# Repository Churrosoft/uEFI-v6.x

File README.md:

# uEFI-v6.x
Speeduino compatible board, features:

* on board CAN
* SD card reader
* x4 ignition pre-drivers
* x4 injection channels
* 2&amp;4 wire IAC
* Accelerometer (ADXL343) / Barometer (BMP280)
* Reverse battery protection and Overvoltage Protection (LM7480-Q1)
* x5 user inputs
* optional BT module (HC-05)
* x3 relay outputs & x1 1.2A output
* x1 boost valve output

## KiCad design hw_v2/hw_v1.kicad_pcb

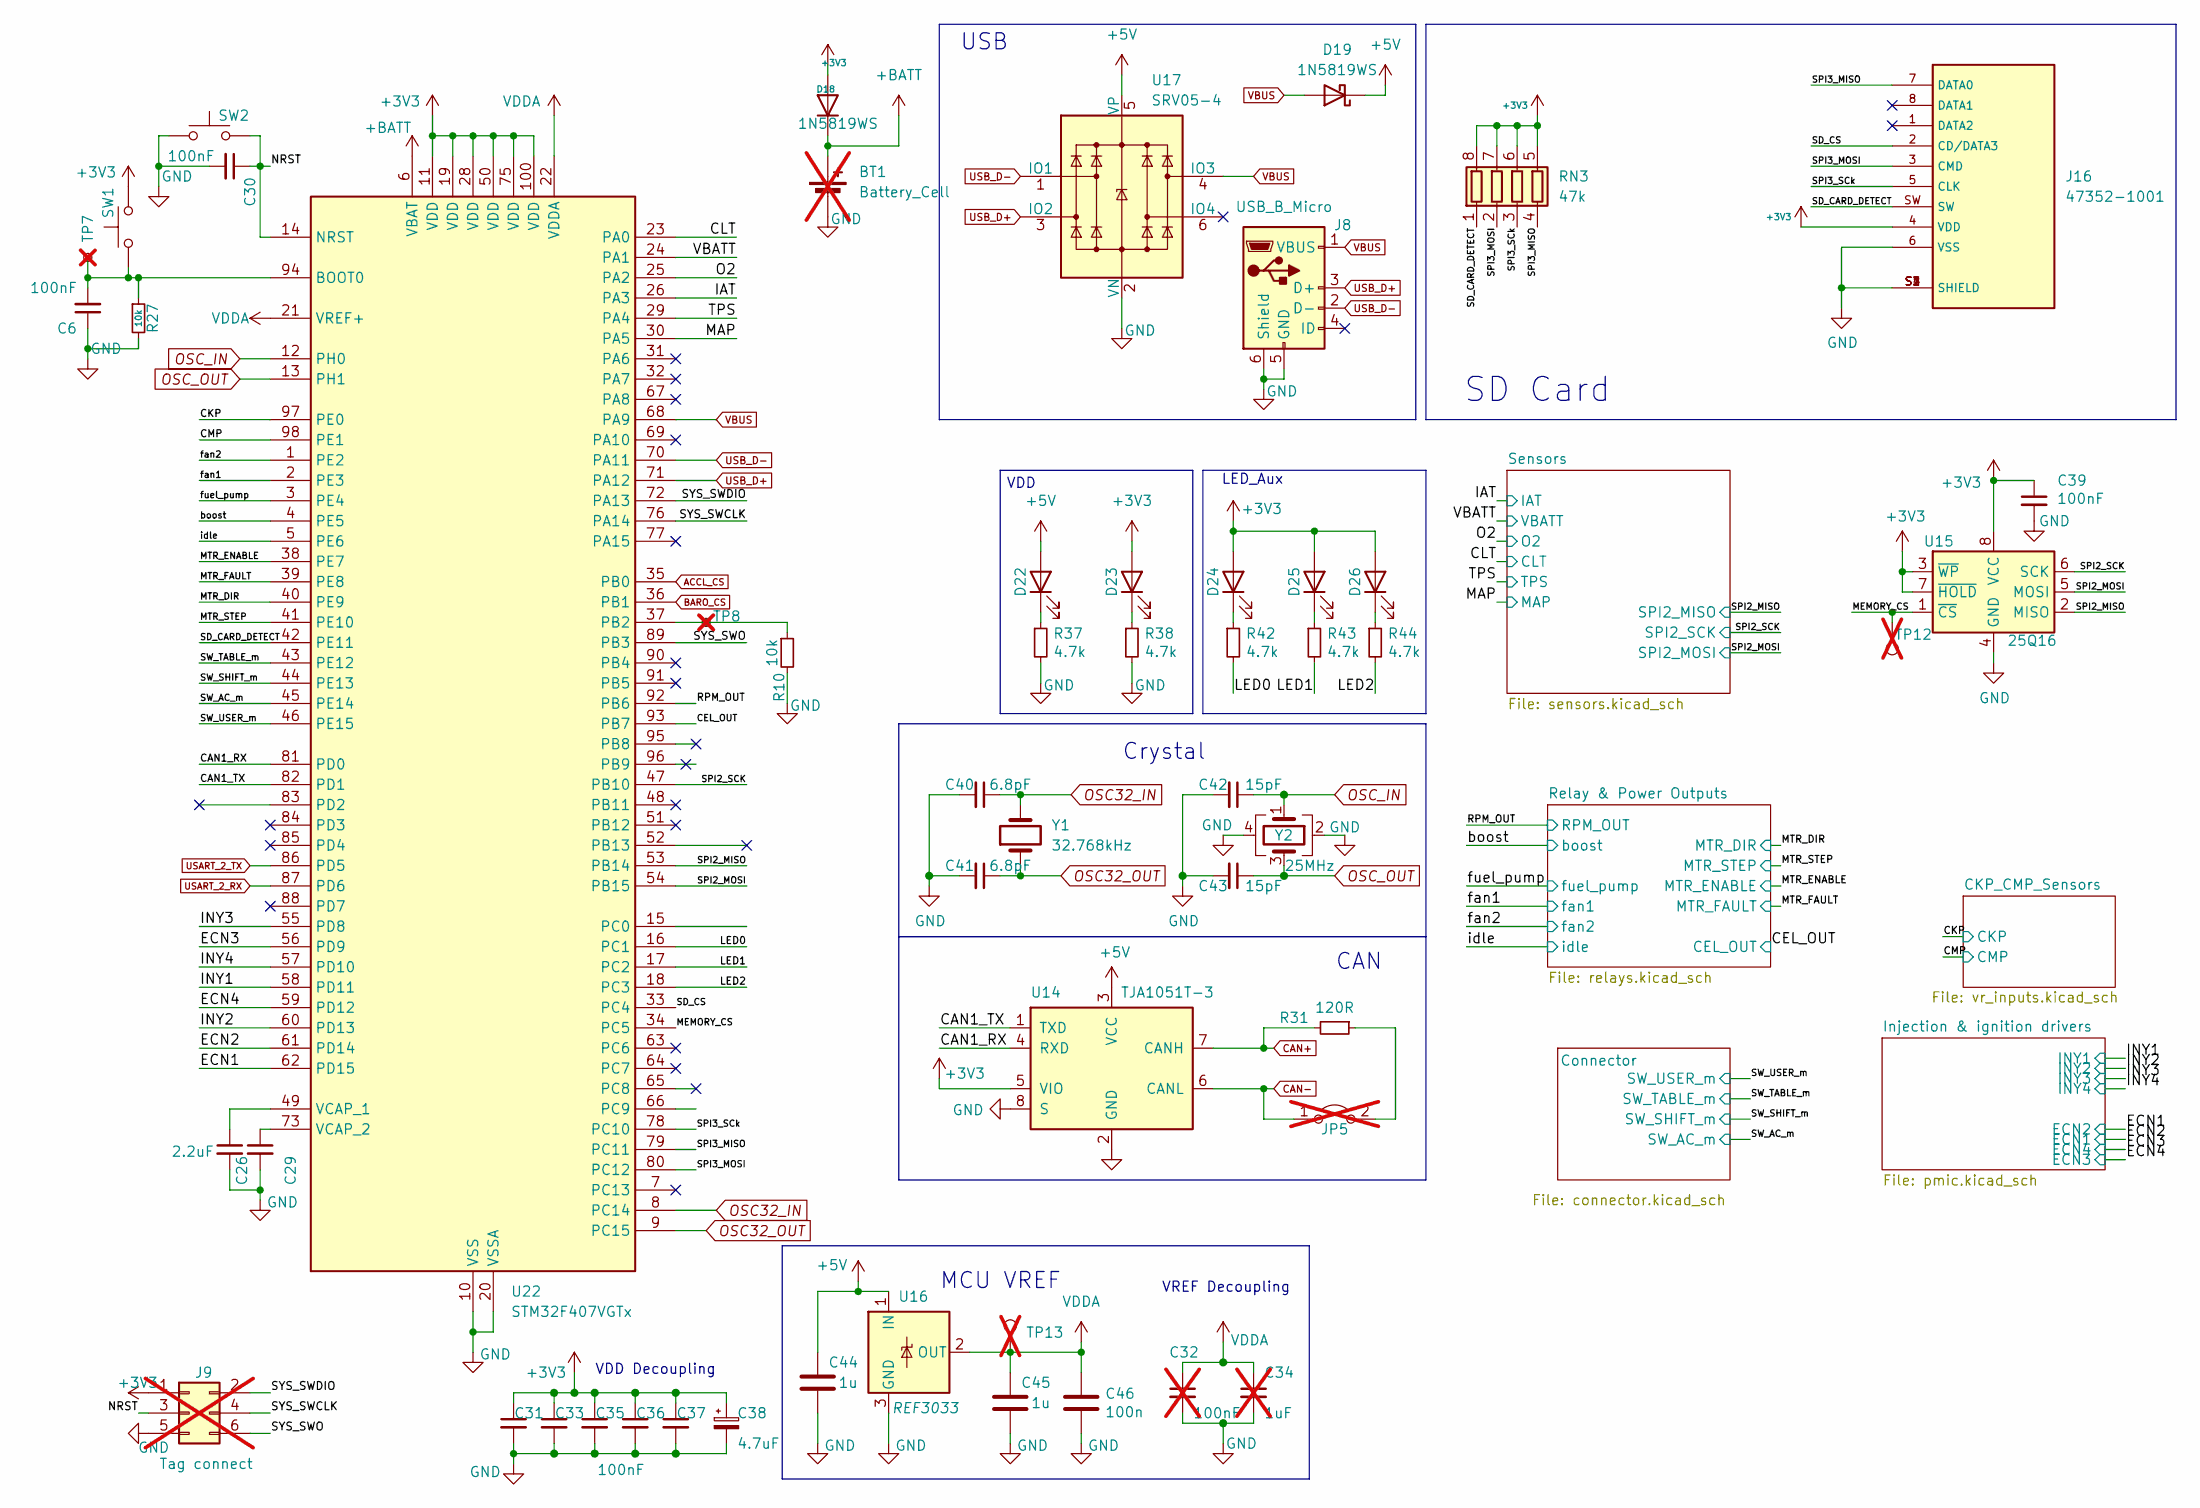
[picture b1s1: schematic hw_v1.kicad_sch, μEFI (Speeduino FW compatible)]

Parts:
BT1: Battery_Cell; JST_EH_B2B-EH-A_1x02_P2.50mm_Vertical; LCSC C722633; not fitted
C6, C30, C31, C33, C35, C36, C37, C39: 100nF; C_0805_2012Metric; LCSC C49678
C26, C29: 2.2uF; C_0805_2012Metric; LCSC C377773
C32: 100nF; C_0805_2012Metric; LCSC C49678; not fitted
C34: 1uF; C_0805_2012Metric; LCSC C28323; not fitted
C38: 4.7uF; C_0805_2012Metric; LCSC C1779
C40, C41: 6.8pF; C_0805_2012Metric; LCSC C282251
C42, C43: 15pF; C_0805_2012Metric; LCSC C1794
C44, C45: 1u; C_0805_2012Metric; LCSC C52923
C46: 100n; C_0805_2012Metric; LCSC C49678
D18: 1N5819WS; D_SOD-323; LCSC C191023
D19: 1N5819WS; D_SOD-323_HandSoldering; LCSC C191023
D22, D23, D24, D25, D26: LED; LED_0805_2012Metric; Manufacturer_Part_Number SML-H12D8TT86C; Digikey Part Number SML-H12D8TT86CCT-ND
J8: USB_B_Micro; USB_Mini-B_Tensility_54-00023_Vertical
J9: Tag connect; Tag-Connect_TC2030-IDC-FP_2x03_P1.27mm_Vertical; not fitted
J16: 47352-1001; PARTREV K; LCSC C293569
JP5: Jumper_2_Open; SolderJumper-2_P1.3mm_Bridged2Bar_Pad1.0x1.5mm; not fitted
R10, R27: 10k; R_0603_1608Metric; LCSC C115324
R31: 120R; R_1206_3216Metric; LCSC C144469
R37, R38, R42, R43, R44: 4.7k; R_0603_1608Metric; LCSC C23162
RN3: 47k; R_Array_Convex_4x0603; LCSC C102673
SW1, SW2: SW_Push; SW_SPST_CK_RS282G05A3; LCSC C2888955
TP7: BOOT0; TestPoint_Pad_D2.0mm; not fitted
TP8: BOOT1; TestPoint_Pad_D2.0mm; not fitted
TP12, TP13: TestPoint; TestPoint_Pad_1.0x1.0mm; not fitted
U14: TJA1051T-3; SOIC-8_3.9x4.9mm_P1.27mm; LCSC C5342108
U15: 25Q16; SOIC-8_5.275x5.275mm_P1.27mm; LCSC C82317
U16: REF3033; SOT-23; LCSC C36658
U17: SRV05-4; SOT-23-6; LCSC C85364
U22: STM32F407VGTx; LQFP-100_14x14mm_P0.5mm; LCSC C12345
Y1: 32.768kHz; Crystal_SMD_2012-2Pin_2.0x1.2mm; LCSC C5381473
Y2: 25MHz; Crystal_SMD_3225-4Pin_3.2x2.5mm; LCSC C9006

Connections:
+3V3: C31.1, C33.1, C35.1, C36.1, C37.1, C38.1, C39.1, D18.2 (A), D23.2 (A), D24.2 (A), D25.2 (A), D26.2 (A), J9.1, J16.4 (VDD), RN3.5 (R4.2), RN3.6 (R3.2), RN3.7 (R2.2), RN3.8 (R1.2), SW1.2, U14.5 (VIO), U15.3 (~WP), U15.7 (~HOLD), U15.8 (VCC), U22.11 (VDD), U22.19 (VDD), U22.28 (VDD), U22.50 (VDD), U22.75 (VDD), U22.100 (VDD); also elsewhere on the board
+5V: C44.1, D19.1 (K), D22.2 (A), U14.3 (VCC), U16.1 (IN), U17.5 (VP); also elsewhere on the board
+BATT: BT1.1 (+), D18.1 (K), U22.6 (VBAT)
/CAN1_RX: U14.4 (RXD), U22.81 (PD0)
/CAN1_TX: U14.1 (TXD), U22.82 (PD1)
/CEL_OUT: U22.93 (PB7); also elsewhere on the board
/CKP: U22.97 (PE0); also elsewhere on the board
/CLT: U22.23 (PA0); also elsewhere on the board
/CMP: U22.98 (PE1); also elsewhere on the board
/ECN1: U22.62 (PD15); also elsewhere on the board
/ECN2: U22.61 (PD14); also elsewhere on the board
/ECN3: U22.56 (PD9); also elsewhere on the board
/ECN4: U22.59 (PD12); also elsewhere on the board
/IAT: U22.26 (PA3); also elsewhere on the board
/INY1: U22.58 (PD11); also elsewhere on the board
/INY2: U22.60 (PD13); also elsewhere on the board
/INY3: U22.55 (PD8); also elsewhere on the board
/INY4: U22.57 (PD10); also elsewhere on the board
/LED0: R42.2, U22.16 (PC1)
/LED1: R43.2, U22.17 (PC2)
/LED2: R44.2, U22.18 (PC3)
/MAP: U22.30 (PA5); also elsewhere on the board
/MEMORY_CS: TP12.1, U15.1 (~CS), U22.34 (PC5)
/MTR_DIR: U22.40 (PE9); also elsewhere on the board
/MTR_ENABLE: U22.38 (PE7); also elsewhere on the board
/MTR_FAULT: U22.39 (PE8); also elsewhere on the board
/MTR_STEP: U22.41 (PE10); also elsewhere on the board
/NRST: C30.1, J9.3, SW2.2, U22.14 (NRST)
/O2: U22.25 (PA2); also elsewhere on the board
/RPM_OUT: U22.92 (PB6); also elsewhere on the board
/SD_CARD_DETECT: J16.SW, RN3.1 (R1.1), U22.42 (PE11)
/SD_CS: J16.2 (CD/DATA3), U22.33 (PC4)
/SPI2_MISO: U15.2 (MISO), U22.53 (PB14); also elsewhere on the board
/SPI2_MOSI: U15.5 (MOSI), U22.54 (PB15); also elsewhere on the board
/SPI2_SCK: U15.6 (SCK), U22.47 (PB10); also elsewhere on the board
/SPI3_MISO: J16.7 (DATA0), RN3.4 (R4.1), U22.79 (PC11)
/SPI3_MOSI: J16.3 (CMD), RN3.2 (R2.1), U22.80 (PC12)
/SPI3_SCk: J16.5 (CLK), RN3.3 (R3.1), U22.78 (PC10)
/SW_AC_m: U22.45 (PE14); also elsewhere on the board
/SW_SHIFT_m: U22.44 (PE13); also elsewhere on the board
/SW_TABLE_m: U22.43 (PE12); also elsewhere on the board
/SW_USER_m: U22.46 (PE15); also elsewhere on the board
/SYS_SWCLK: J9.4, U22.76 (PA14)
/SYS_SWDIO: J9.2, U22.72 (PA13)
/SYS_SWO: J9.6, U22.89 (PB3)
/TPS: U22.29 (PA4); also elsewhere on the board
/VBATT: U22.24 (PA1); also elsewhere on the board
/boost: U22.4 (PE5); also elsewhere on the board
/fan1: U22.2 (PE3); also elsewhere on the board
/fan2: U22.1 (PE2); also elsewhere on the board
/fuel_pump: U22.3 (PE4); also elsewhere on the board
/idle: U22.5 (PE6); also elsewhere on the board
ACCL_CS: U22.35 (PB0); also elsewhere on the board
BARO_CS: U22.36 (PB1); also elsewhere on the board
CAN+: R31.2, U14.7 (CANH); also elsewhere on the board
CAN-: JP5.1 (A), U14.6 (CANL); also elsewhere on the board
GND: BT1.2 (-), C6.1, C26.2, C29.2, C30.2, C31.2, C32.2, C33.2, C34.2, C35.2, C36.2, C37.2, C38.2, C39.2, C40.2, C41.2, C42.2, C43.2, C44.2, C45.2, C46.2, J8.5 (GND), J8.6 (Shield), J9.5, J16.6 (VSS), J16.S1 (SHIELD), J16.S2 (SHIELD), J16.S3 (SHIELD), J16.S4 (SHIELD), R10.2, R27.2, R37.2, R38.2, SW2.1, U14.2 (GND), U14.8 (S), U15.4 (GND), U16.3 (GND), U17.2 (VN), U22.10 (VSS), U22.20 (VSSA), U22.27 (VSS), U22.74 (VSS), U22.99 (VSS), Y2.2, Y2.4; also elsewhere on the board
unnamed: D22.1 (K), R37.1
unnamed: D23.1 (K), R38.1
unnamed: D24.1 (K), R42.1
unnamed: D25.1 (K), R43.1
unnamed: D26.1 (K), R44.1
unnamed: JP5.2 (B), R31.1
unnamed: C6.2, R27.1, SW1.1, TP7.1, U22.94 (BOOT0)
unnamed: R10.1, TP8.1, U22.37 (PB2)
unnamed: C26.1, U22.49 (VCAP_1)
unnamed: C29.1, U22.73 (VCAP_2)
OSC32_IN: C40.1, U22.8 (PC14), Y1.2
OSC32_OUT: C41.1, U22.9 (PC15), Y1.1
OSC_IN: C42.1, U22.12 (PH0), Y2.1
OSC_OUT: C43.1, U22.13 (PH1), Y2.3
USART_2_RX: U22.87 (PD6); also elsewhere on the board
USART_2_TX: U22.86 (PD5); also elsewhere on the board
USB_D+: J8.3 (D+), U17.3 (IO2), U22.71 (PA12); also elsewhere on the board
USB_D-: J8.2 (D-), U17.1 (IO1), U22.70 (PA11); also elsewhere on the board
VBUS: D19.2 (A), J8.1 (VBUS), U17.4 (IO3), U22.68 (PA9)
VDDA: C32.1, C34.1, C45.1, C46.1, TP13.1, U16.2 (OUT), U22.21 (VREF+), U22.22 (VDDA)

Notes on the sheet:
Crystal
VDD Decoupling
MCU VREF
VDD
LED_Aux
SD Card
USB
CAN
VREF Decoupling

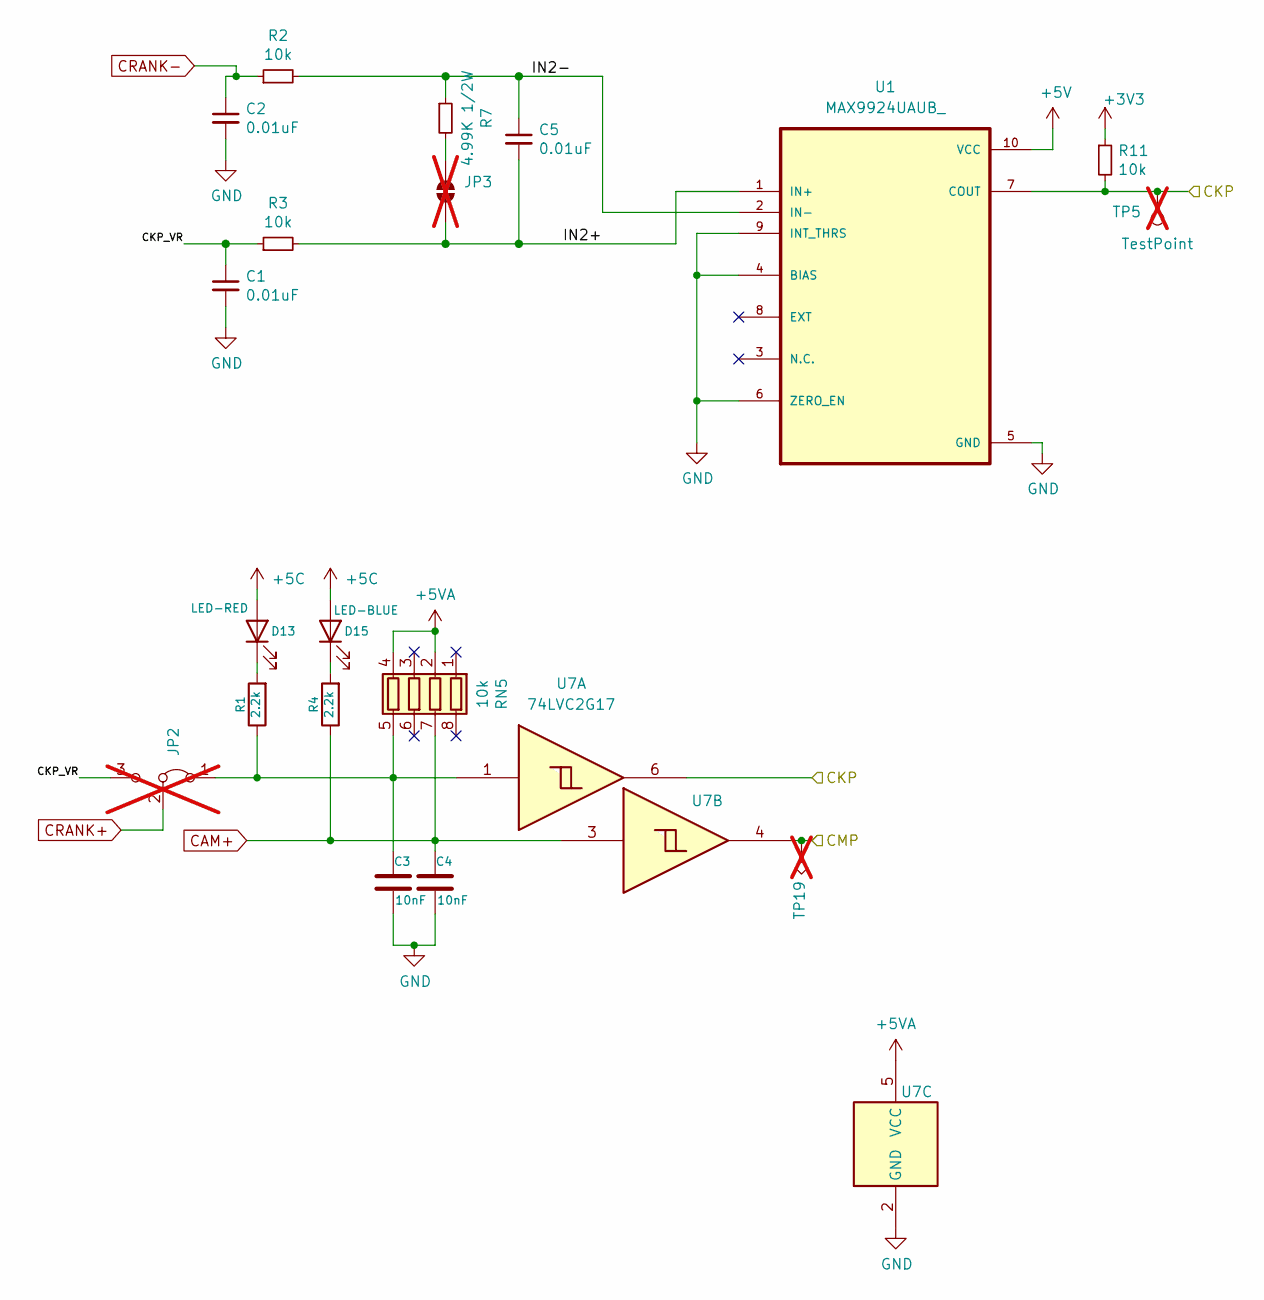
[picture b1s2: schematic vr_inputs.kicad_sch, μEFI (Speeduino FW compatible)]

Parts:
C1, C2, C5: 0.01uF; C_0805_2012Metric; LCSC C100042
C3, C4: 10nF; C_0603_1608Metric; Part # C0603C103K1RACTU; LCSC C57112
D13: LED-RED; LED_0603_1608Metric; LCSC C2286
D15: LED-BLUE; LED_0603_1608Metric; LCSC C2286
JP2: Jumper_3_Bridged12; SolderJumper-3_P1.3mm_Bridged12_Pad1.0x1.5mm; not fitted
JP3: SolderJumper_2_Open; SolderJumper-2_P1.3mm_Open_RoundedPad1.0x1.5mm; not fitted
R1, R4: 2.2k; R_0603_1608Metric; Part # RMCF0603FT2K20; LCSC C4190
R2, R3, R11: 10k; R_0603_1608Metric; LCSC C115324
R7: 4.99K 1/2W; R_0805_2012Metric; LCSC C2933454
RN5: 10k; R_Array_Convex_4x0603; Part # YC164-JR-0710KL; LCSC C29718
TP5: TestPoint; TestPoint_Pad_1.0x1.0mm; not fitted
TP19: TestPoint_Alt; TestPoint_Pad_1.0x1.0mm; not fitted
U1: MAX9924UAUB_; SOP50P490X110-10N
U7: 74LVC2G17; SOT-363_SC-70-6; LCSC C80500

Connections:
+3V3: R11.1; also elsewhere on the board
+5C: D13.2 (A), D15.2 (A), RN5.2 (R2.1), RN5.4 (R4.1), U7.5 (VCC); also elsewhere on the board
+5V: U1.10 (VCC); also elsewhere on the board
/CKP: R11.2, TP5.1, U1.7 (COUT), U7.6; also elsewhere on the board
/CKP_CMP_Sensors/CKP_VR: C1.1, JP2.3 (B), R3.1
/CKP_CMP_Sensors/IN2+: C5.2, JP3.1 (A), R3.2, U1.1 (IN+)
/CKP_CMP_Sensors/IN2-: C5.1, R2.2, R7.1, U1.2 (IN-)
/CMP: TP19.1, U7.4; also elsewhere on the board
CAM+: C4.1, R4.1, RN5.7 (R2.2), U7.3; also elsewhere on the board
CRANK+: JP2.2 (C); also elsewhere on the board
CRANK-: C2.1, R2.1; also elsewhere on the board
GND: C1.2, C2.2, C3.2, C4.2, U1.4 (BIAS), U1.5 (GND), U1.6 (ZERO_EN), U1.9 (INT_THRS), U7.2 (GND); also elsewhere on the board
unnamed: D13.1 (K), R1.2
unnamed: D15.1 (K), R4.2
unnamed: C3.1, JP2.1 (A), R1.1, RN5.5 (R4.2), U7.1
unnamed: JP3.2 (B), R7.2

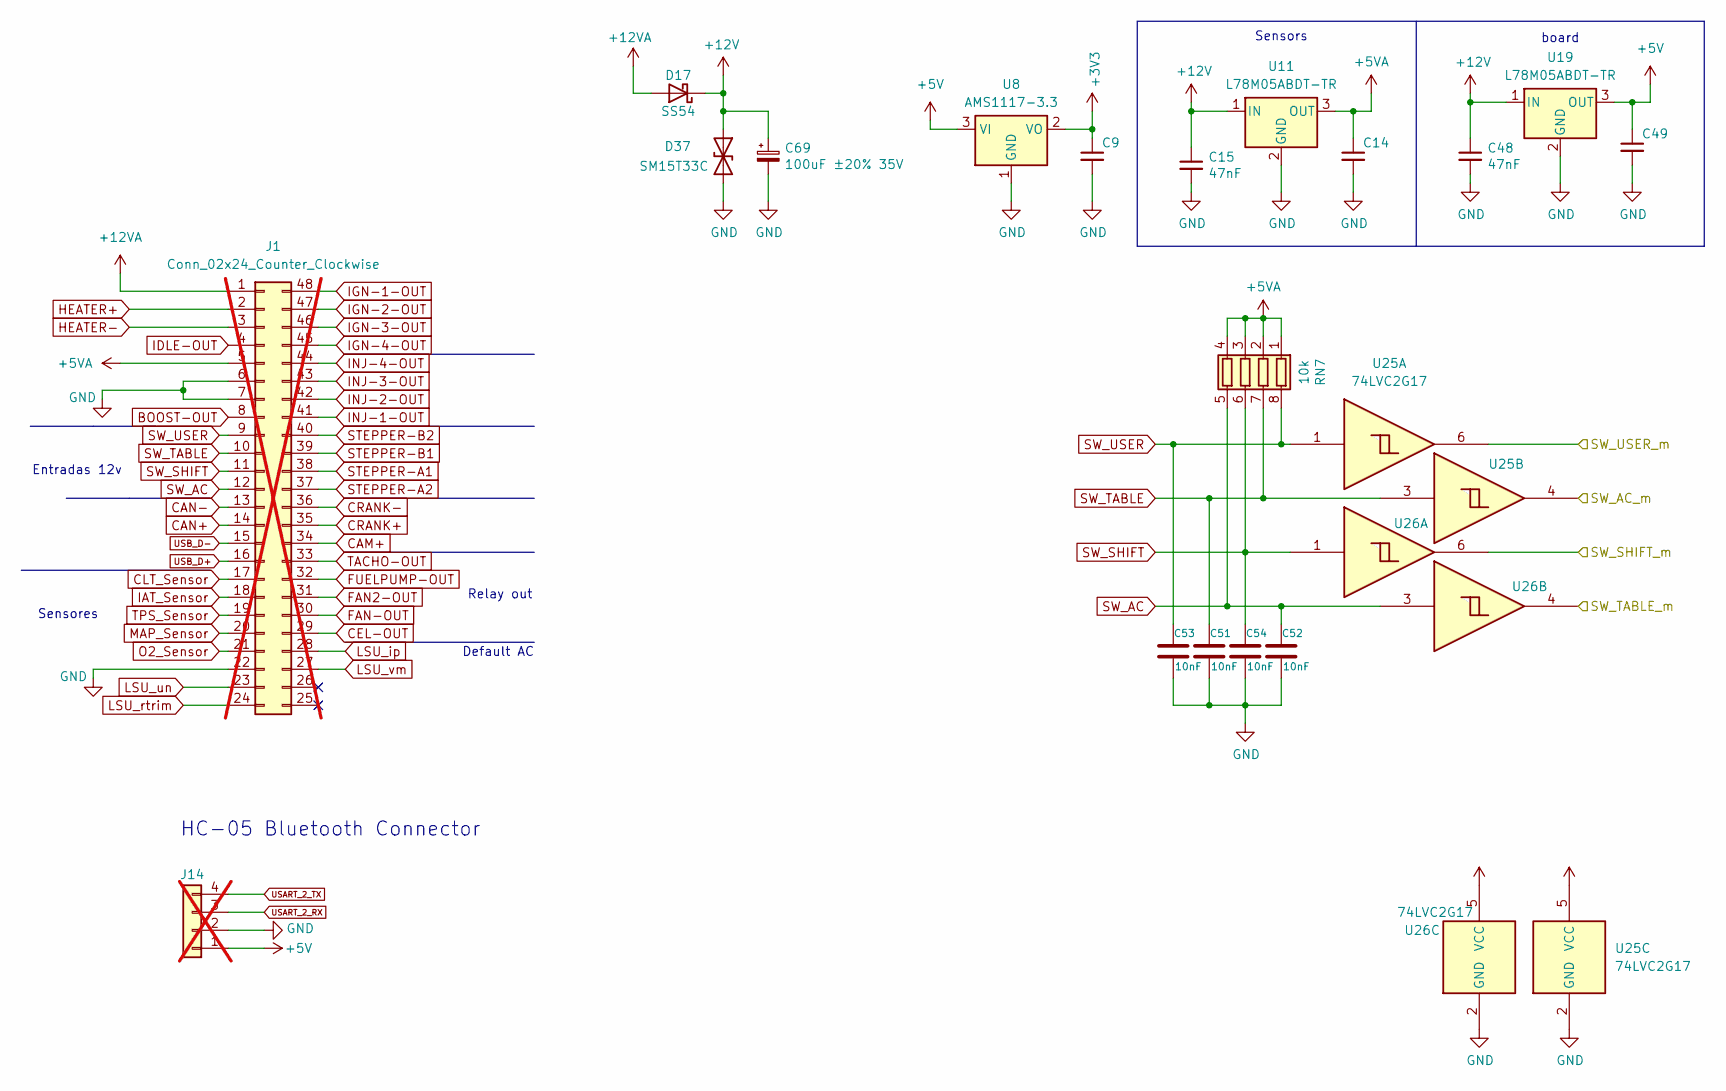
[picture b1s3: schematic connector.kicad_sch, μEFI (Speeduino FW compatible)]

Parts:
C9, C14, C49: 100nF; C_0805_2012Metric; LCSC C49678
C15, C48: 47nF; C_0603_1608Metric; LCSC C1622
C51, C52, C53, C54: 10nF; C_0603_1608Metric; Part # C0603C103K1RACTU; LCSC C57112
C69: 100uF ±20% 35V; CP_Elec_6.3x7.7; LCSC C141427
D17: SS54; D_SMA; LCSC C22452
D37: SM15T33C; D_SMC; LCSC C133707
J1: Conn_02x24_Counter_Clockwise; Molex_48p; not fitted
J14: Conn_01x04; PinHeader_1x04_P2.54mm_Vertical; not fitted
RN7: 10k; R_Array_Convex_4x0603; Part # YC164-JR-0710KL; LCSC C29718
U8: AMS1117-3.3; SOT-223-3_TabPin2; LCSC C2992570
U11, U19: L78M05ABDT-TR; TO-252-2; LCSC C58069
U25, U26: 74LVC2G17; SOT-363_SC-70-6

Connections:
+3V3: C9.1, U8.2 (VO), U25.5 (VCC), U26.5 (VCC); also elsewhere on the board
+5C: C14.1, J1.5, RN7.1 (R1.1), RN7.2 (R2.1), RN7.3 (R3.1), RN7.4 (R4.1), U11.3 (OUT); also elsewhere on the board
+5V: C49.1, J14.1, U8.3 (VI), U19.3 (OUT); also elsewhere on the board
+12VA: D17.2 (A), J1.1
/SW_AC_m: U25.4; also elsewhere on the board
/SW_SHIFT_m: U26.6; also elsewhere on the board
/SW_TABLE_m: U26.4; also elsewhere on the board
/SW_USER_m: U25.6; also elsewhere on the board
BOOST-OUT: J1.8; also elsewhere on the board
CAM+: J1.34; also elsewhere on the board
CAN+: J1.14; also elsewhere on the board
CAN-: J1.13; also elsewhere on the board
CEL-OUT: J1.29; also elsewhere on the board
CLT_Sensor: J1.17; also elsewhere on the board
CRANK+: J1.35; also elsewhere on the board
CRANK-: J1.36; also elsewhere on the board
FAN2-OUT: J1.31; also elsewhere on the board
FAN-OUT: J1.30; also elsewhere on the board
FUELPUMP-OUT: J1.32; also elsewhere on the board
GND: C9.2, C14.2, C15.2, C48.2, C49.2, C51.2, C52.2, C53.2, C54.2, C69.2, D37.2 (A2), J1.6, J1.7, J1.22, J14.2, U8.1 (GND), U11.2 (GND), U19.2 (GND), U25.2 (GND), U26.2 (GND); also elsewhere on the board
HEATER+: C15.1, C48.1, C69.1, D17.1 (K), D37.1 (A1), J1.2, U11.1 (IN), U19.1 (IN); also elsewhere on the board
HEATER-: J1.3; also elsewhere on the board
IAT_Sensor: J1.18; also elsewhere on the board
IDLE-OUT: J1.4; also elsewhere on the board
IGN-1-OUT: J1.48; also elsewhere on the board
IGN-2-OUT: J1.47; also elsewhere on the board
IGN-3-OUT: J1.46; also elsewhere on the board
IGN-4-OUT: J1.45; also elsewhere on the board
INJ-1-OUT: J1.41; also elsewhere on the board
INJ-2-OUT: J1.42; also elsewhere on the board
INJ-3-OUT: J1.43; also elsewhere on the board
INJ-4-OUT: J1.44; also elsewhere on the board
LSU_ip: J1.28; also elsewhere on the board
LSU_rtrim: J1.24; also elsewhere on the board
LSU_un: J1.23; also elsewhere on the board
LSU_vm: J1.27; also elsewhere on the board
MAP_Sensor: J1.20; also elsewhere on the board
O2_Sensor: J1.21; also elsewhere on the board
STEPPER-A1: J1.38; also elsewhere on the board
STEPPER-A2: J1.37; also elsewhere on the board
STEPPER-B1: J1.39; also elsewhere on the board
STEPPER-B2: J1.40; also elsewhere on the board
SW_AC: C52.1, J1.12, RN7.5 (R4.2), U26.3
SW_SHIFT: C54.1, J1.11, RN7.6 (R3.2), U26.1
SW_TABLE: C51.1, J1.10, RN7.7 (R2.2), U25.3
SW_USER: C53.1, J1.9, RN7.8 (R1.2), U25.1
TACHO-OUT: J1.33; also elsewhere on the board
TPS_Sensor: J1.19; also elsewhere on the board
USART_2_RX: J14.3; also elsewhere on the board
USART_2_TX: J14.4; also elsewhere on the board
USB_D+: J1.16; also elsewhere on the board
USB_D-: J1.15; also elsewhere on the board

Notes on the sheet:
Sensors
HC-05 Bluetooth Connector
Relay out
Sensores
Default AC
Entradas 12v
board

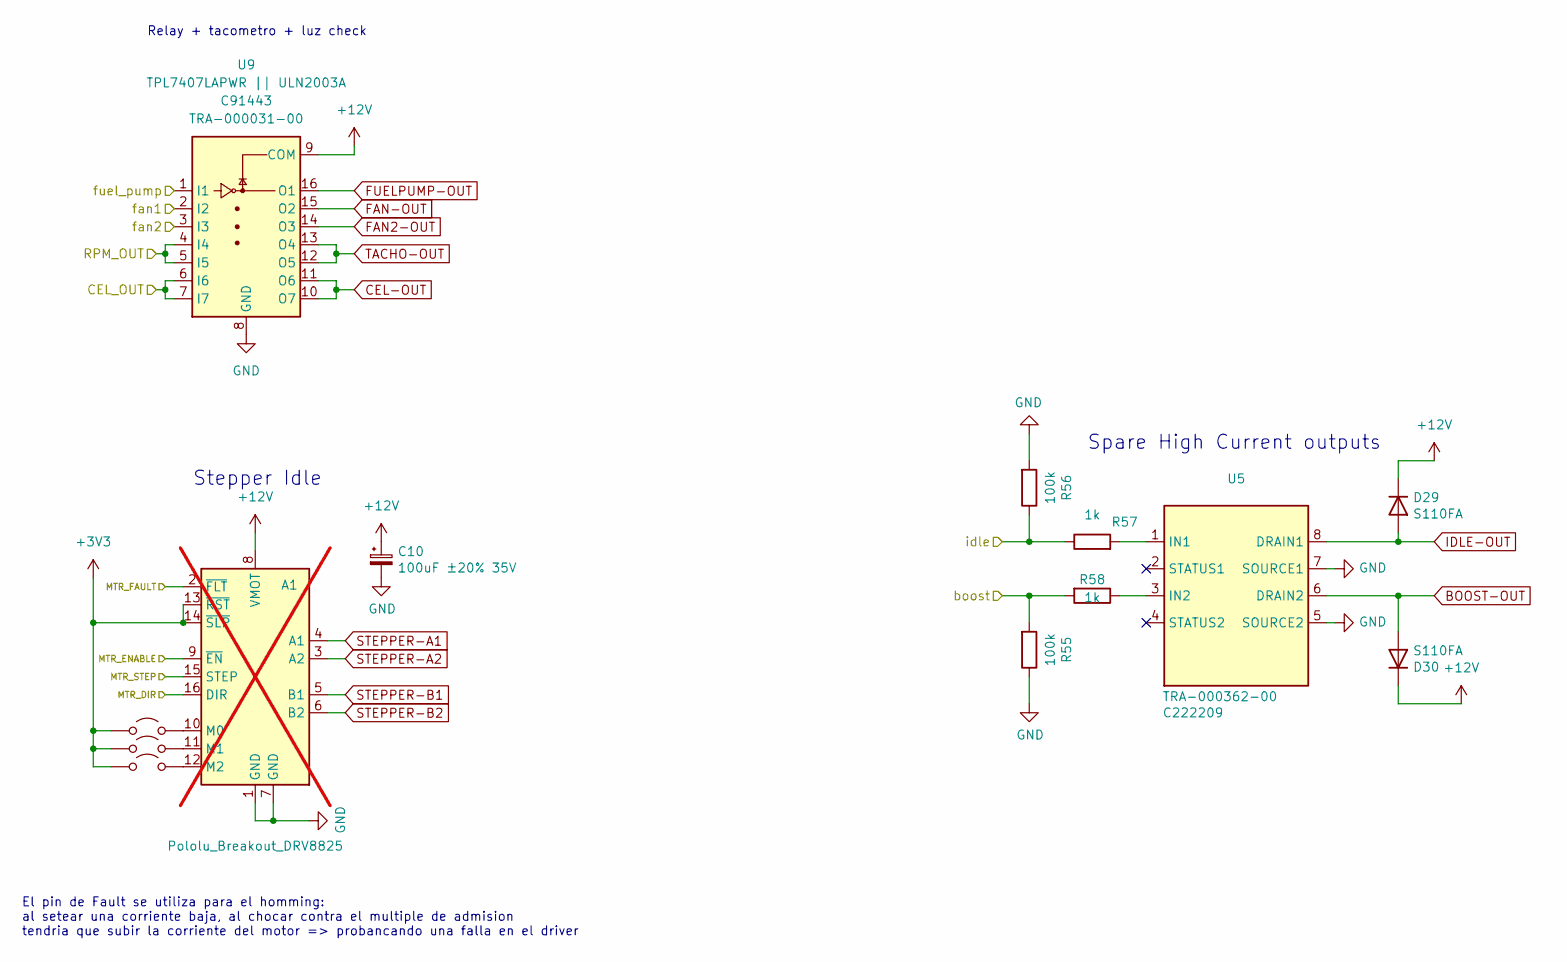
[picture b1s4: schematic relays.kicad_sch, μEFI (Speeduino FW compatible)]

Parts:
A1: Pololu_Breakout_DRV8825; Pololu_Breakout-16_15.2x20.3mm; not fitted
C10: 100uF ±20% 35V; CP_Elec_6.3x7.7; LCSC C141427
D29, D30: S110FA; D_SOD-123F; Manufacturer_Part_Number S110FA; Digikey Part Number S110FACT-ND
JP6, JP7, JP8: Jumper_2_Open; SolderJumper-2_P1.3mm_Open_Pad1.0x1.5mm
R55, R56: 100k; R_0603_1608Metric; LCSC C25803
R57, R58: 1k; R_0603_1608Metric; Manufacturer_Part_Number RC0805FR-071KL; Digikey Part Number 311-1.00KCRCT-ND
U5: SO-8_3.9x4.9mm_P1.27mm; LCSC C222209
U9: TPL7407LAPWR || ULN2003A; TSSOP-16_4.4x5mm_P0.65mm; LCSC C91443

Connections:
+3V3: A1.13 (~RST), A1.14 (~SLP), JP6.1 (A), JP7.1 (A), JP8.1 (A); also elsewhere on the board
/CEL_OUT: U9.6 (I6), U9.7 (I7); also elsewhere on the board
/MTR_DIR: A1.16 (DIR); also elsewhere on the board
/MTR_ENABLE: A1.9 (~EN); also elsewhere on the board
/MTR_FAULT: A1.2 (~FLT); also elsewhere on the board
/MTR_STEP: A1.15 (STEP); also elsewhere on the board
/RPM_OUT: U9.4 (I4), U9.5 (I5); also elsewhere on the board
/boost: R55.2, R58.2; also elsewhere on the board
/fan1: U9.2 (I2); also elsewhere on the board
/fan2: U9.3 (I3); also elsewhere on the board
/fuel_pump: U9.1 (I1); also elsewhere on the board
/idle: R56.1, R57.1; also elsewhere on the board
BOOST-OUT: D30.2 (A), U5.6 (DRAIN2); also elsewhere on the board
CEL-OUT: U9.10 (O7), U9.11 (O6); also elsewhere on the board
FAN2-OUT: U9.14 (O3); also elsewhere on the board
FAN-OUT: U9.15 (O2); also elsewhere on the board
FUELPUMP-OUT: U9.16 (O1); also elsewhere on the board
GND: A1.1 (GND), A1.7 (GND), C10.2, R55.1, R56.2, U5.5 (SOURCE2), U5.7 (SOURCE1), U9.8 (GND); also elsewhere on the board
HEATER+: A1.8 (VMOT), C10.1, D29.1 (K), D30.1 (K), U9.9 (COM); also elsewhere on the board
IDLE-OUT: D29.2 (A), U5.8 (DRAIN1); also elsewhere on the board
unnamed: A1.10 (M0), JP6.2 (B)
unnamed: A1.11 (M1), JP7.2 (B)
unnamed: A1.12 (M2), JP8.2 (B)
unnamed: R57.2, U5.1 (IN1)
unnamed: R58.1, U5.3 (IN2)
STEPPER-A1: A1.4 (A1); also elsewhere on the board
STEPPER-A2: A1.3 (A2); also elsewhere on the board
STEPPER-B1: A1.5 (B1); also elsewhere on the board
STEPPER-B2: A1.6 (B2); also elsewhere on the board
TACHO-OUT: U9.12 (O5), U9.13 (O4); also elsewhere on the board

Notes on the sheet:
Spare High Current outputs
El pin de Fault se utiliza para el homming: al setear una corriente baja, al chocar contra el multiple de admision tendria que subir la corriente del motor => probancando una falla en el driver
Relay + tacometro + luz check
Stepper Idle

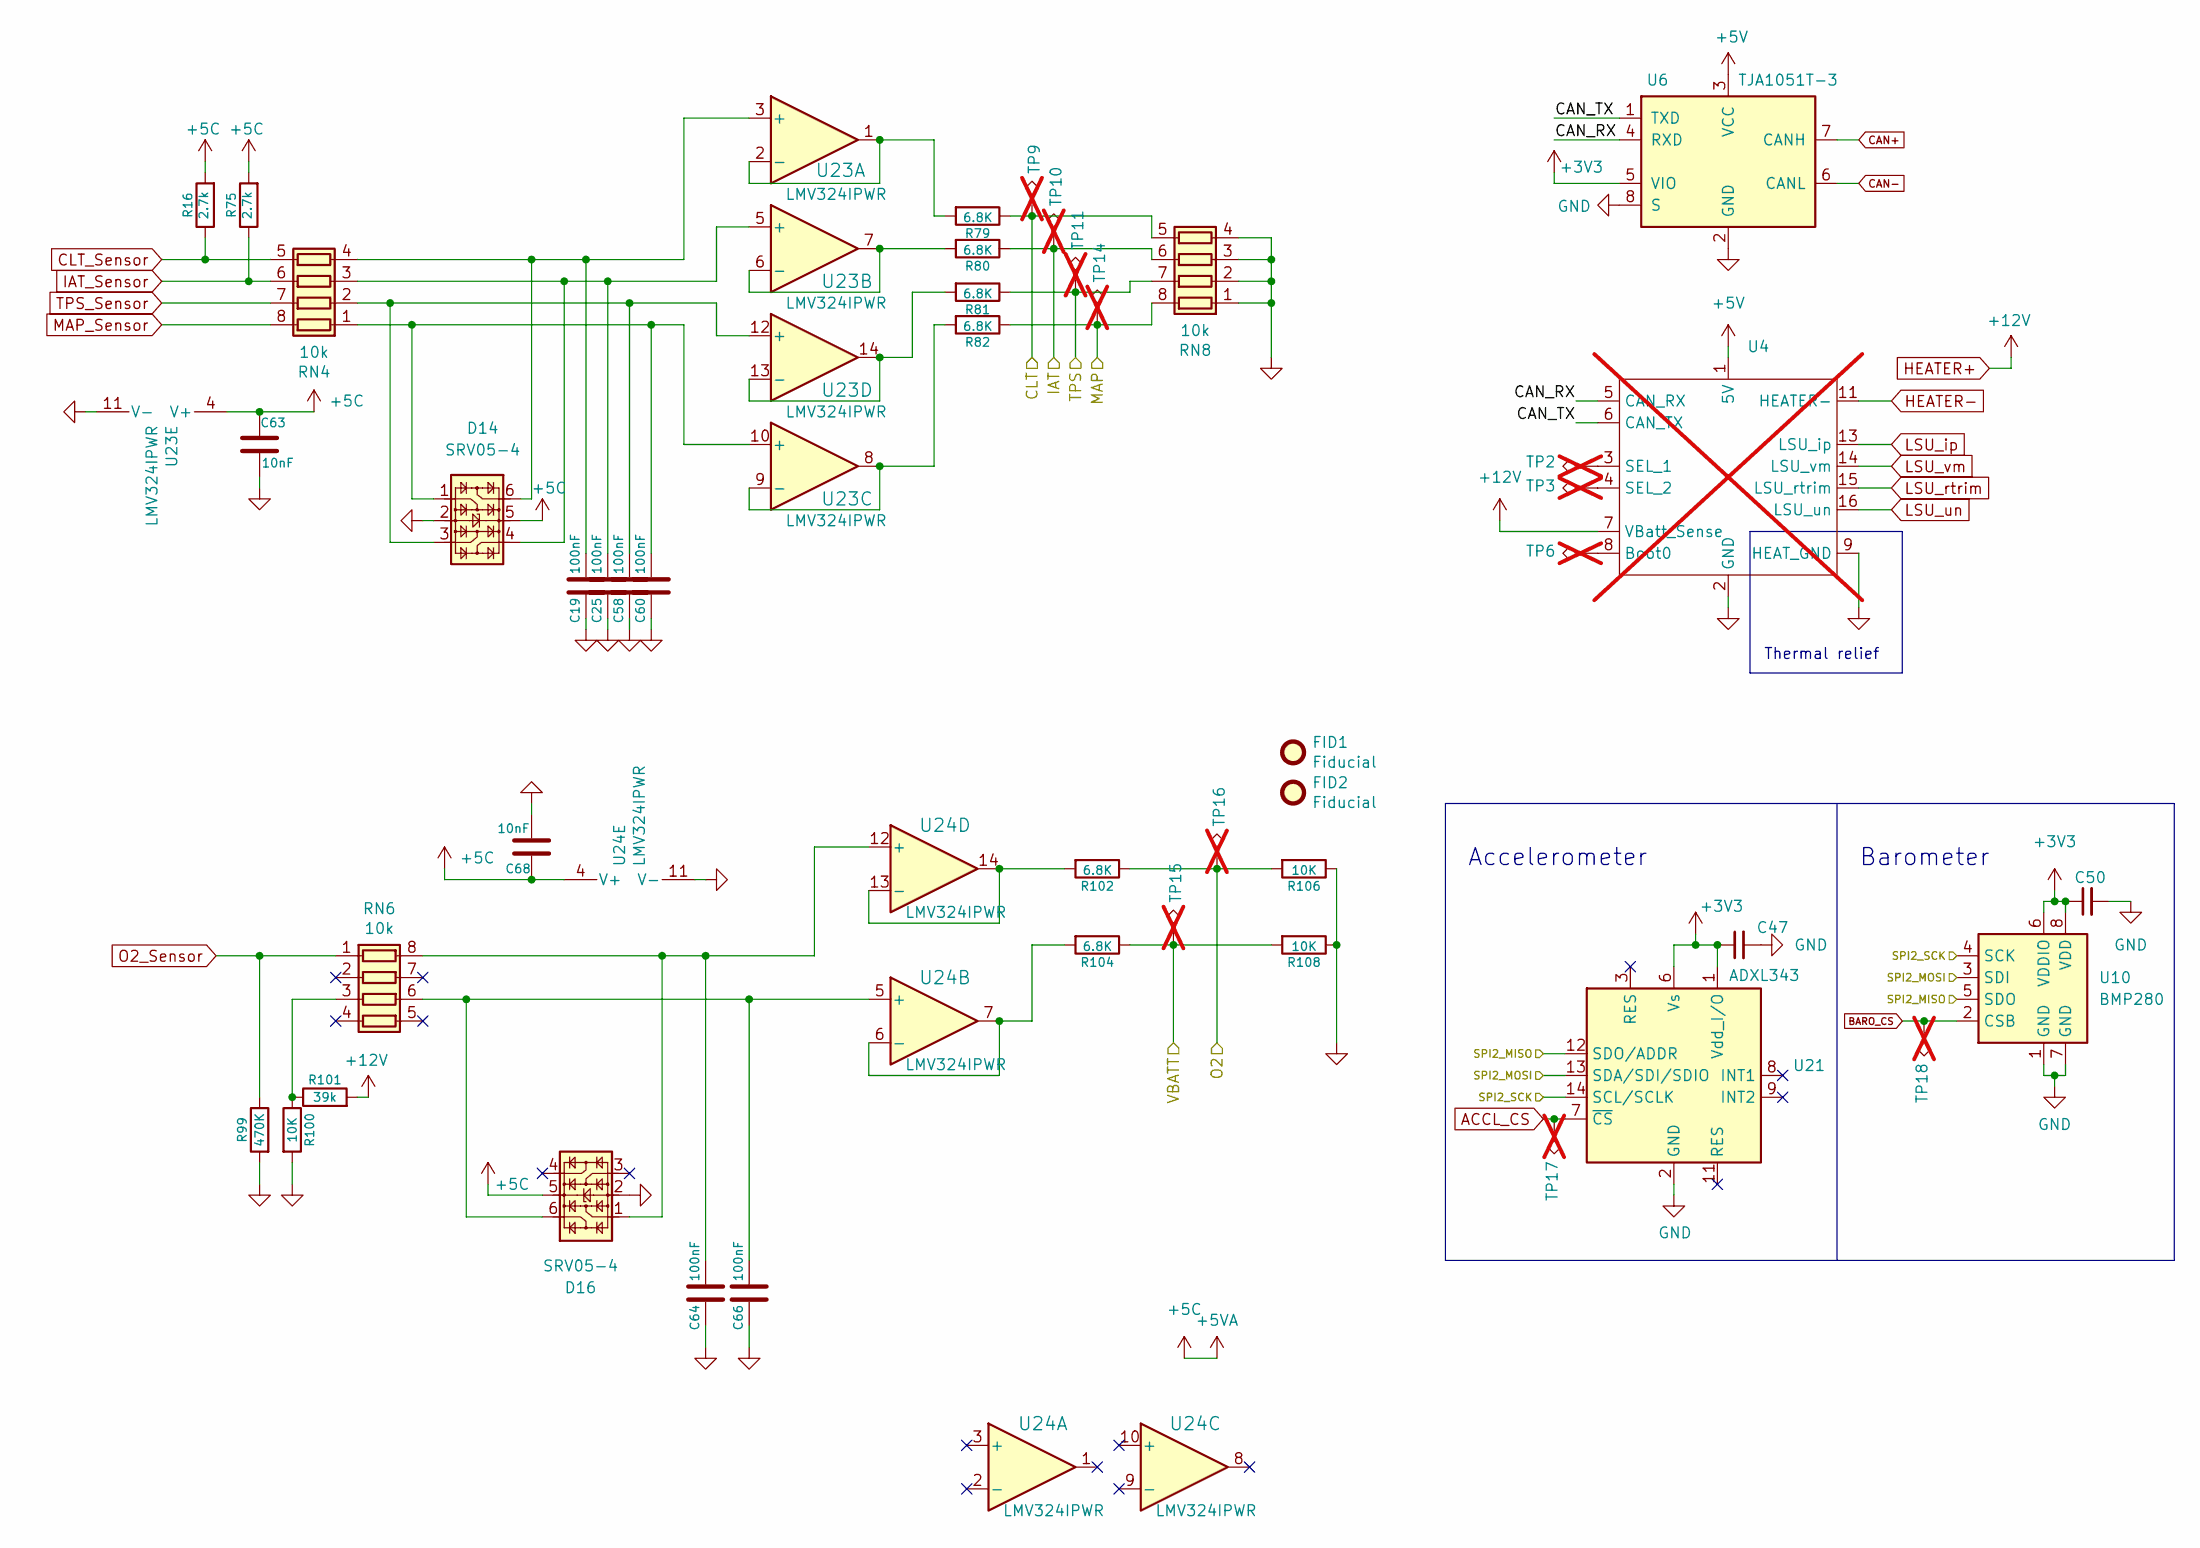
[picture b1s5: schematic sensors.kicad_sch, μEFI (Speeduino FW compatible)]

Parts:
C19, C25, C58, C60, C64, C66: 100nF; C_0402_1005Metric; LCSC C1525
C47, C50: 100nF; C_0805_2012Metric; LCSC C49678
C63, C68: 10nF; C_0603_1608Metric; Part # C0603C103K1RACTU; LCSC C57112
D14, D16: SRV05-4; SOT-363_SC-70-6; LCSC C85364
FID1, FID2: Fiducial; Fiducial_0.5mm_Mask1mm; Part # DNP
R16, R75: 2.7k; R_0603_1608Metric; Part # RMCF0603FT2K70; LCSC C13167
R79, R80, R81, R82, R102, R104: 6.8K; R_0603_1608Metric; LCSC C23212
R99: 470K; R_0603_1608Metric; LCSC C25790
R100, R106, R108: 10K; R_0603_1608Metric; Part # RMCF0603JT10K0; LCSC C25804
R101: 39k; R_0603_1608Metric; Part # RC0603FR-0739KL; LCSC C23153
RN4, RN6, RN8: 10k; R_Array_Convex_4x0603; Part # YC164-JR-0710KL; LCSC C29718
TP2, TP3, TP6, TP9, TP10, TP11, TP14, TP15, TP16, TP17, TP18: TestPoint_Alt; TestPoint_Pad_1.0x1.0mm; not fitted
U4: WBO-module; not fitted
U6: TJA1051T-3; SOIC-8_3.9x4.9mm_P1.27mm; LCSC C5342108
U10: BMP280; Bosch_LGA-8_2x2.5mm_P0.65mm_ClockwisePinNumbering; LCSC C83291
U21: ADXL343; LGA-14_3x5mm_P0.8mm_LayoutBorder1x6y; Manufacturer_Part_Number ADXL343BCCZ-RL; Digikey Part Number ADXL343BCCZ-RLCT-ND
U23, U24: LMV324IPWR; TSSOP-14_4.4x5mm_P0.65mm; Part # MCP6004T-I/ST

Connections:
+3V3: C47.1, C50.1, U6.5 (VIO), U10.6 (VDDIO), U10.8 (VDD), U21.1 (Vdd_I/O), U21.6 (Vs); also elsewhere on the board
+5C: C63.1, C68.1, D14.5, D16.5, R16.2, R75.2, U23.4 (V+), U24.4 (V+); also elsewhere on the board
+5V: U4.1 (5V), U6.3 (VCC); also elsewhere on the board
/CLT: R79.1, RN8.5 (R4.2), TP9.1; also elsewhere on the board
/IAT: R80.1, RN8.6 (R3.2), TP10.1; also elsewhere on the board
/MAP: R82.1, RN8.8 (R1.2), TP14.1; also elsewhere on the board
/O2: R102.1, R106.2, TP16.1; also elsewhere on the board
/SPI2_MISO: U10.5 (SDO), U21.12 (SDO/ADDR); also elsewhere on the board
/SPI2_MOSI: U10.3 (SDI), U21.13 (SDA/SDI/SDIO); also elsewhere on the board
/SPI2_SCK: U10.4 (SCK), U21.14 (SCL/SCLK); also elsewhere on the board
/Sensors/CAN_RX: U4.5 (CAN_RX), U6.4 (RXD)
/Sensors/CAN_TX: U4.6 (CAN_TX), U6.1 (TXD)
/TPS: R81.1, RN8.7 (R2.2), TP11.1; also elsewhere on the board
/VBATT: R104.1, R108.2, TP15.1; also elsewhere on the board
ACCL_CS: TP17.1, U21.7 (~CS); also elsewhere on the board
BARO_CS: TP18.1, U10.2 (CSB); also elsewhere on the board
CAN+: U6.7 (CANH); also elsewhere on the board
CAN-: U6.6 (CANL); also elsewhere on the board
CLT_Sensor: R16.1, RN4.5 (R4.2); also elsewhere on the board
GND: C19.2, C25.2, C47.2, C50.2, C58.2, C60.2, C63.2, C64.2, C66.2, C68.2, D14.2, D16.2, R99.2, R100.2, R106.1, R108.1, RN8.1 (R1.1), RN8.2 (R2.1), RN8.3 (R3.1), RN8.4 (R4.1), U4.2 (GND), U4.9 (HEAT_GND), U4.10 (HEAT_GND2), U6.2 (GND), U6.8 (S), U10.1 (GND), U10.7 (GND), U21.2 (GND), U21.4 (GND), U21.5 (GND), U23.11 (V-), U24.11 (V-); also elsewhere on the board
HEATER+: R101.2, U4.7 (VBatt_Sense); also elsewhere on the board
HEATER-: U4.11 (HEATER-), U4.12 (HEATER-); also elsewhere on the board
IAT_Sensor: R75.1, RN4.6 (R3.2); also elsewhere on the board
LSU_ip: U4.13 (LSU_ip); also elsewhere on the board
LSU_rtrim: U4.15 (LSU_rtrim); also elsewhere on the board
LSU_un: U4.16 (LSU_un); also elsewhere on the board
LSU_vm: U4.14 (LSU_vm); also elsewhere on the board
MAP_Sensor: RN4.8 (R1.2); also elsewhere on the board
unnamed: C60.1, D14.1, RN4.1 (R1.1), U23.10 (+)
unnamed: C58.1, D14.3, RN4.2 (R2.1), U23.12 (+)
unnamed: C25.1, D14.4, RN4.3 (R3.1), U23.5 (+)
unnamed: C19.1, D14.6, RN4.4 (R4.1), U23.3 (+)
unnamed: C64.1, D16.1, RN6.8 (R1.2), U24.12 (+)
unnamed: R100.1, R101.1, RN6.3 (R3.1)
unnamed: C66.1, D16.6, RN6.6 (R3.2), U24.5 (+)
unnamed: TP6.1, U4.8 (Boot0)
unnamed: TP2.1, U4.3 (SEL_1)
unnamed: TP3.1, U4.4 (SEL_2)
unnamed: R79.2, U23.1, U23.2 (-)
unnamed: R80.2, U23.6 (-), U23.7
unnamed: R82.2, U23.8, U23.9 (-)
unnamed: R81.2, U23.13 (-), U23.14
unnamed: R104.2, U24.6 (-), U24.7
unnamed: R102.2, U24.13 (-), U24.14
O2_Sensor: R99.1, RN6.1 (R1.1); also elsewhere on the board
TPS_Sensor: RN4.7 (R2.2); also elsewhere on the board

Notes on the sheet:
Barometer
Accelerometer
Thermal relief

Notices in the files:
hw_v1/connector.kicad_sch:
CERN-OHL-S-2.0 license
